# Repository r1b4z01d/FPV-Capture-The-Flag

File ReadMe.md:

#Intro
  This game is intended to extend the curently available interactive FPV drone games. This could possibly be extended to be used as an led gate that changes color as each pilot passes through it. 

##Game Directions
  Up to four pilots can play at a time. As many flags as posible spread out. The objective is to fly as close to each flag as possible until the flag changes to the players color. My initial (untested) idea was to have no set course and pilots would openly fly what ever path to what ever flag next. If a head on collision is to happen each pilot must bail to their right. 

##Hardware required
* Arduino Pro Mini 5V 16Mhz 
* RX5805 Module
* Polu 5V Regulator
* WS2811B LED Strip

##Game Options
* Pilot VTX Channels
* Pilot Colors
* Number of LEDs
* RSSI Trigger
* LED Update speed

##To do: 
* Split/cleanup code
* Finalize PDB design
* Finish the readme
* How to video
* Add Bluetooth, WIFI and/or UWB
* Create Mobile App
* Update LICENSE 

##Thanks
With out @voroshkov's work on [Chorus-RF-Laptimer](https://github.com/voroshkov/Chorus-RF-Laptimer) this never could have been done. I will split out his code and will include the MIT notice.

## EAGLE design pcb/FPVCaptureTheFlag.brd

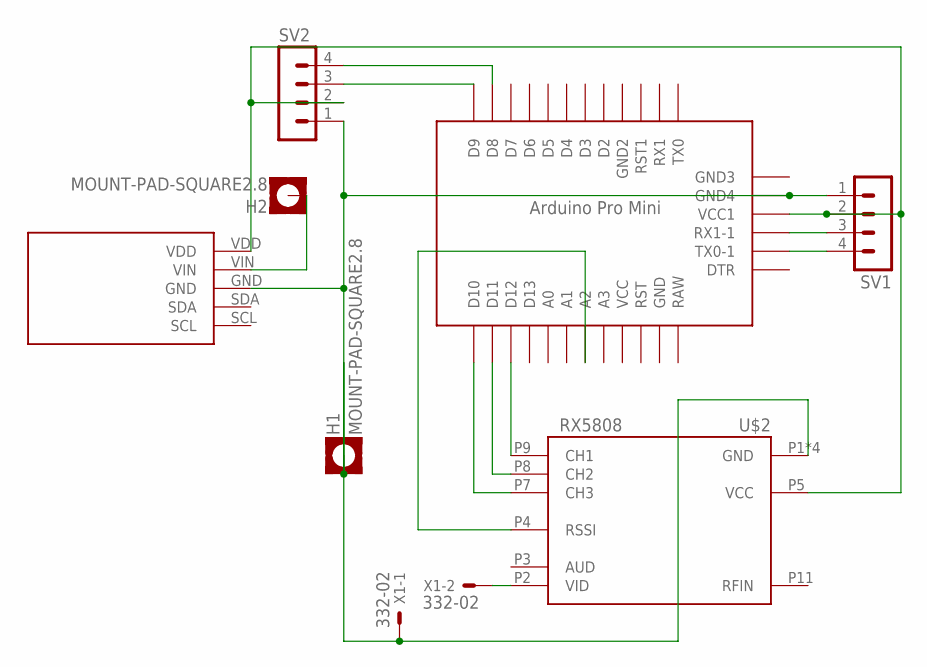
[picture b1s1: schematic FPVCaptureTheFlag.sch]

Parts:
H1, H2: MOUNT-PAD-SQUARE2.8; 2,8-PAD-SQUARE
SV1, SV2: MA04-1
U$1: ABK-PRO-MINI
U$2: RX5808
U$3: POLOLU_MINIMU9_V2THROUGHHOLE; POLOLU_MINIMU9_V2
X1: 332-02

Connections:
unnamed: U$1.D12, U$2.P9 (CH1)
unnamed: U$1.D11, U$2.P8 (CH2)
unnamed: U$1.D10, U$2.P7 (CH3)
unnamed: U$1.A2, U$2.P4 (RSSI)
unnamed: SV2.4, U$1.D8
unnamed: SV2.3, U$1.D9
unnamed: H2.B2,8, U$3.VIN
unnamed: SV1.3, U$1.RX1-1
unnamed: SV1.4, U$1.TX0-1
unnamed: H1.B2,8, SV1.1, SV2.1, U$1.GND3 (GND4), U$2.P1 (GND), U$2.P6 (GND), U$2.P10 (GND), U$2.P12 (GND), U$3.GND, X1.1
unnamed: U$2.P2 (VID), X1.2
unnamed: SV1.2, SV2.2, U$1.VCC1, U$2.P5 (VCC), U$3.VDD

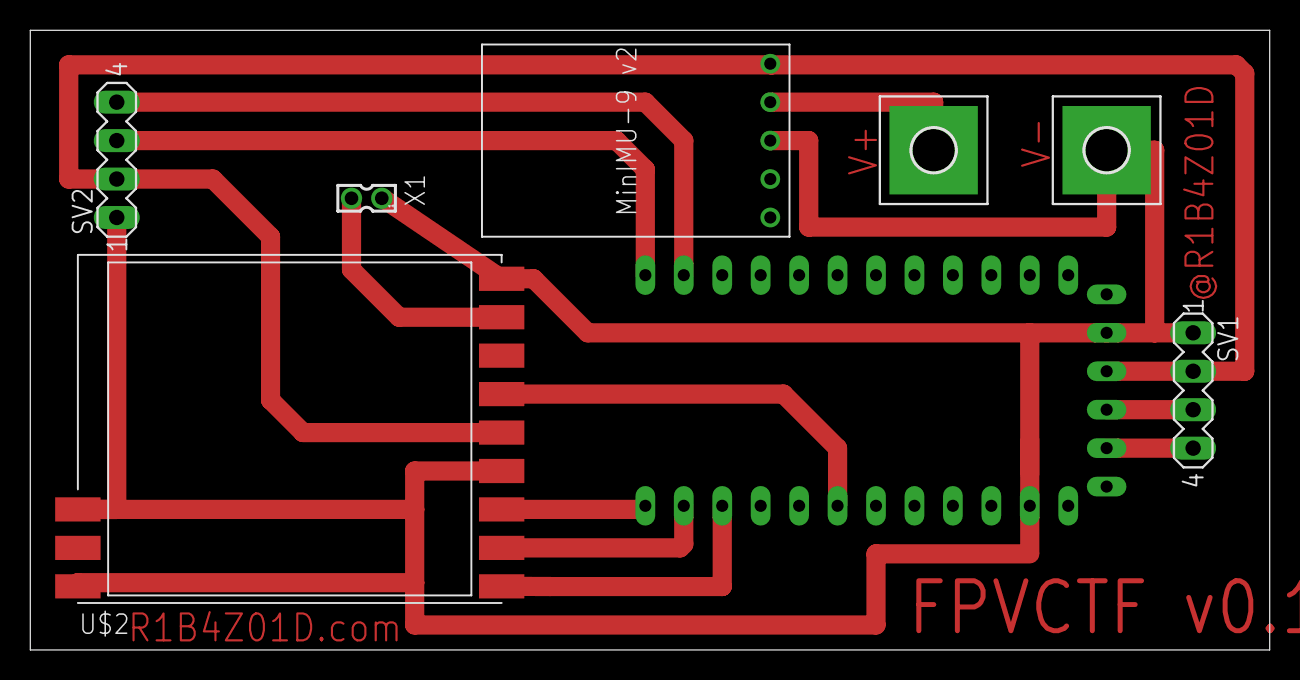
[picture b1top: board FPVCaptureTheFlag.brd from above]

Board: 2 copper layers, 81.9 x 40.9 mm, 8 parts (0 on the bottom side), 12 nets.

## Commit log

2018-03-07 First
